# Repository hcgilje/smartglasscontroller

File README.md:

# smartglasscontroller
A shield for Arduino Mega to control 5 smartglass break out boards
This shield was made to work together with the smart glass controller breakout boads: https://github.com/OBauck/smart-glass-controller-breakout

It consists of 5 CAT connectors, one DMX output and a RTC module.

Created for my KORO commission for Drammen Tinghus 2023.

The files are made with KiCad 7.0
The boards where fabricated at JLCPBC using the files in the Production folder

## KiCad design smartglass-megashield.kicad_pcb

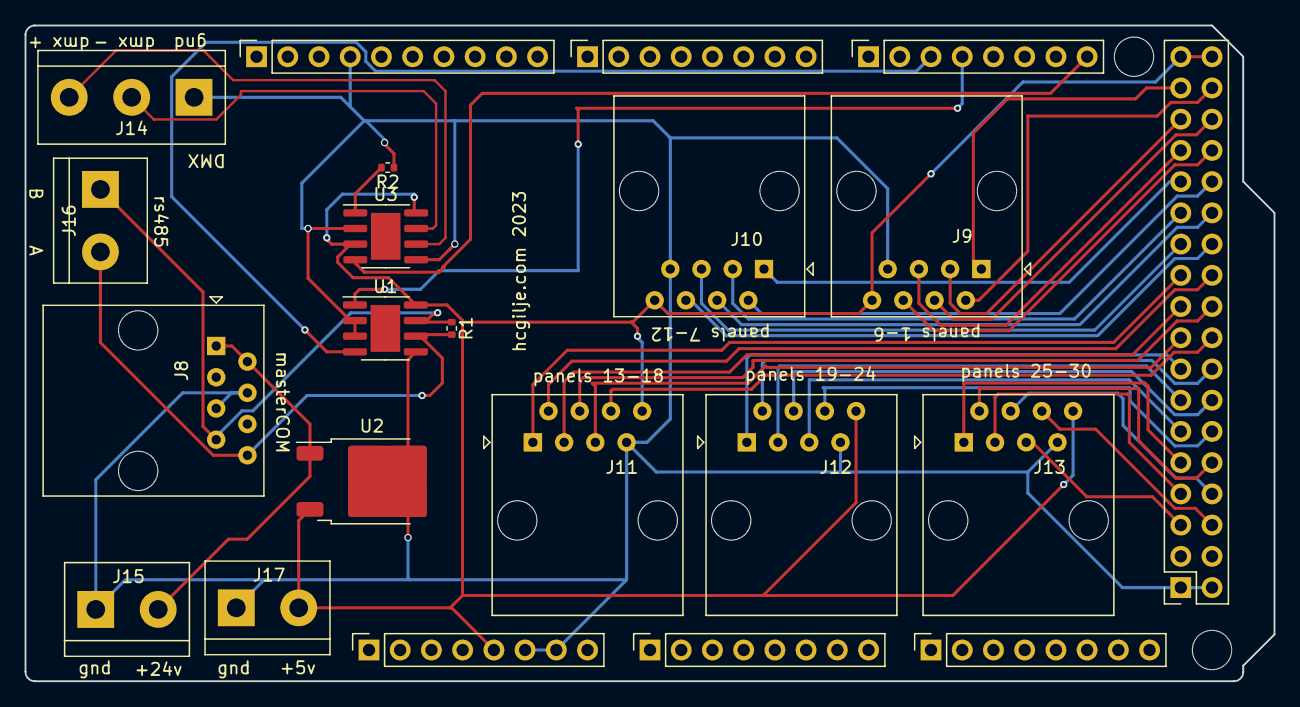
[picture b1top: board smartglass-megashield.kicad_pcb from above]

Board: 2 copper layers, 101.6 x 53.3 mm, 24 parts (0 on the bottom side), 41 nets.

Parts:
J1: Power; PinSocket_1x08_P2.54mm_Vertical
J2: PWM; PinSocket_1x10_P2.54mm_Vertical
J3, J5: Analog; PinSocket_1x08_P2.54mm_Vertical
J4: PWM; PinSocket_1x08_P2.54mm_Vertical
J6: Communication; PinSocket_1x08_P2.54mm_Vertical
J7: Digital; PinSocket_2x18_P2.54mm_Vertical
J8, J9, J10, J11, J12, J13: RJ45; RJ45_Amphenol_54602-x08_Horizontal
J14: DMX; TerminalBlock_bornier-3_P5.08mm
J15: 24v; TerminalBlock_bornier-2_P5.08mm
J16: rs485; TerminalBlock_bornier-2_P5.08mm
J17: +5v; TerminalBlock_bornier-2_P5.08mm
MH5, MH6: MountingHole_3.2mm
R1: 120R; R_0402_1005Metric
R2: 100R; R_0402_1005Metric
U1, U3: MAX485E; SOIC-8-1EP_3.9x4.9mm_P1.27mm_EP2.41x3.81mm
U2: LM78M05_TO252; TO-252-2

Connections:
+5V: J1.5, J7.35, J7.36, J9.8, J10.8, J11.8, J12.8, J13.8, J17.2, U1.8 (VCC), U2.3 (VO), U3.3 (DE), U3.8 (VCC)
+24V: J8.1, J8.2, J15.2, U2.1 (VI)
A: J8.8, J16.2, R1.2, U1.6 (A)
B: J8.7, J16.1, R1.1, U1.7 (B)
DMX+: J14.3, U3.6 (A)
DMX-: J14.2, U3.7 (B)
GND: J1.6, J1.7, J2.4, J7.1, J7.2, J8.4, J8.5, J9.7, J10.7, J11.7, J12.7, J13.7, J14.1, J15.1, J17.1, R2.1, U1.2 (~RE), U1.3 (DE), U1.5 (GND), U2.2 (GND), U3.2 (~RE), U3.5 (GND)
unnamed: R2.2, U3.1 (RO)
O1: J7.33, J9.1
O2: J7.34, J9.2
O3: J7.31, J9.3
O4: J7.32, J9.4
O5: J7.29, J9.5
O6: J7.30, J9.6
O7: J7.27, J10.1
O8: J7.28, J10.2
O9: J7.25, J10.3
O10: J7.26, J10.4
O11: J7.23, J10.5
O12: J7.24, J10.6
O13: J7.21, J11.1
O14: J7.22, J11.2
O15: J7.19, J11.3
O16: J7.20, J11.4
O17: J7.17, J11.5
O18: J7.18, J11.6
O19: J7.15, J12.1
O20: J7.16, J12.2
O21: J7.13, J12.3
O22: J7.14, J12.4
O23: J7.11, J12.5
O24: J7.12, J12.6
O25: J7.9, J13.1
O26: J7.10, J13.2
O27: J7.7, J13.3
O28: J7.8, J13.4
O29: J7.5, J13.5
O30: J7.6, J13.6
dmx input: J6.8, U3.4 (DI)
sRX: J6.4, U1.1 (RO)
sTX: J6.3, U1.4 (DI)

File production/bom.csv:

Designator,Footprint,Quantity,Value,LCSC Part #
J1,PinSocket_1x08_P2.54mm_Vertical,1,Power,
"J10, J11, J12, J13, J8, J9",RJ45_Amphenol_54602-x08_Horizontal,6,RJ45,
J14,TerminalBlock_bornier-3_P5.08mm,1,DMX,
J15,TerminalBlock_bornier-2_P5.08mm,1,24v,
J16,TerminalBlock_bornier-2_P5.08mm,1,rs485,
J17,TerminalBlock_bornier-2_P5.08mm,1,+5v,
J2,PinSocket_1x10_P2.54mm_Vertical,1,PWM,
"J3, J5",PinSocket_1x08_P2.54mm_Vertical,2,Analog,
J4,PinSocket_1x08_P2.54mm_Vertical,1,PWM,
J6,PinSocket_1x08_P2.54mm_Vertical,1,Communication,
J7,PinSocket_2x18_P2.54mm_Vertical,1,Digital,
R1,0402,1,120R,
R2,0402,1,100R,
"U1, U3",SOIC-8-1EP_3.9x4.9mm_P1.27mm_EP2.41x3.81mm,2,MAX485E,
U2,TO-252-2,1,LM78M05_TO252,
